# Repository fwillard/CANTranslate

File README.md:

# CANTranslate

## Overview

CANTranslate is a bridge solution that enables seamless communication ArduPilot devices using DroneCAN protocol and ODrive motor controllers using CANSimple protocol. It translates CAN bus messages between these two protocols in real-time, allowing for integration of these otherwise incompatible systems.

## Features

- Bidirectional translation between DroneCAN and CANSimple protocols
- Custom STM32F205 Based Hardware
- Support for critical message types from both protocols

## Hardware

CANTranslate runs on a custom PCB based on:

- STM32F205RGT6 microcontroller
- SN65HVD230 CAN Transciever

## Software

The project is written in C with the following components:

- Protocol parsers for both DroneCAN and CANSimple
- Message translation logic
- STM32 HAL CAN peripheral

## Protocol Support

### DroneCAN Messages

- [X] Node status messages
- [ ] Actuator commands 
- [ ] Sensor feedback

### CANSimple Messages

- [ ] Motor commands
- [ ] Encoder feedback
- [ ] Controller status
- [ ] Error codes

## License

This project uses dual licensing:

- **Software**: The software is licensed under the MIT License.
- **Hardware**: The hardware design files (schematics, PCB layouts, etc.) are licensed under the CERN Open Hardware License v2 - Permissive.

See the `LICENSE.md` file for the complete license text for both components.

## Contact

For questions and support, please open an issue on the GitHub repository.

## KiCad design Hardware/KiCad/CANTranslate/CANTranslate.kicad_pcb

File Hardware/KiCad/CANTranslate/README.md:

# CANTranslate – Hardware Design

## Overview

The hardware design for **CANTranslate** facilitates physical interfacing and electrical translation between multiple CAN bus systems. This includes power management, bus isolation, transceivers, and microcontroller integration for reliable embedded CAN communication.

## Features

* Dual SN65HVD230 CAN transceivers (CAN 2.0)&#x20;
* STM32F205RGT6 microcontroller
* Power input via USB or 5V pin on the CAN header
* Power source selection using TPS2116DRL (USB VBUS prioritized)
* Debug interface (SWD)

## Hardware Design Files

The following files are included in the `/Hardware/KiCad/CANTranslate` directory:

* `CANTranslate.kicad_pro`
* `CANTranslate.kicad_sch` – Schematic file
* `CANTranslate.kicad_pcb` – PCB layout
* `CustomParts.kicad_sym` – Custom symbol library
* `KMR223G LFG.STEP` – 3D model of tactile switch
* `fabrication-toolkit-options.json` – Fabrication preferences
* `fp-lib-table` – Footprint library table
* `sym-lib-table` – Symbol library table

## Power Requirements
* Power Inputs:
    * 5V from USB VBUS (primary source, with ESD protection)

    * 5V from the CAN header power pin (secondary source, no ESD protection)

* Power Selection:
    * The board uses a TPS2116DRL power multiplexer to automatically select the power source. When both USB and CAN header power are connected, the TPS2116DRL prioritizes USB VBUS, ensuring safe and seamless switching without back-feeding either source.

* Voltage Regulation:
    * The selected 5V supply is regulated down to 3.3V using an AMS1117-3.3 linear voltage regulator, providing stable power for the STM32F205RGT6 MCU and the SN65HVD230 CAN transceivers.

* Protection Features:
    * The USB power input includes ESD protection to safeguard against electrostatic discharge events.

## Toolchain

* **EDA Software**: KiCad 9.x

## Licensing

Hardware design files are released under the **CERN Open Hardware License v2** - Permissive

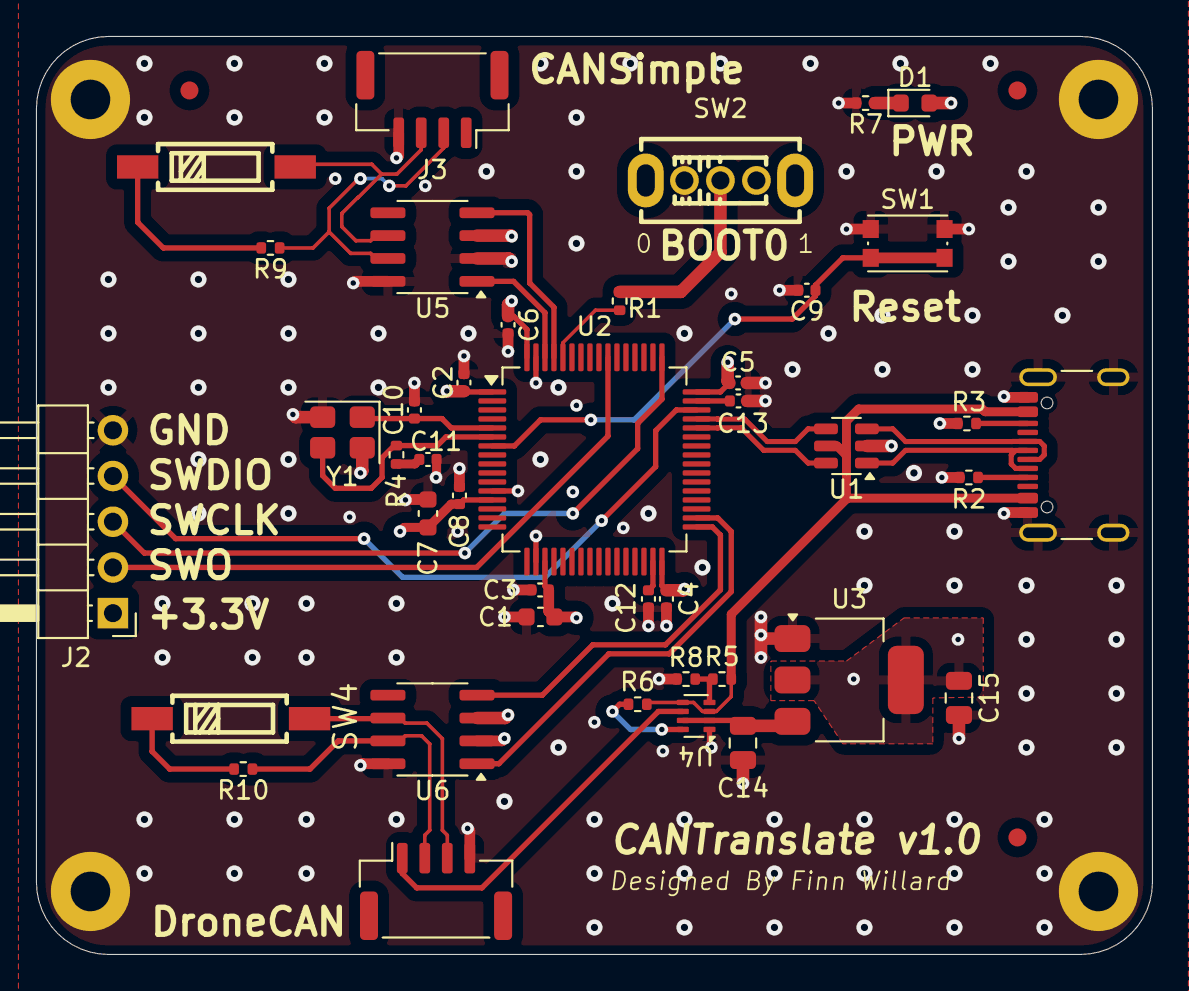
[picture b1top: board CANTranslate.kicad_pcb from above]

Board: 4 copper layers, 62.0 x 51.0 mm, 48 parts (0 on the bottom side), 35 nets.

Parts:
C1: 10u; C_0603_1608Metric
C2, C3, C4, C5, C6, C8, C9: 100n; C_0402_1005Metric
C7: 1u; C_0603_1608Metric
C10, C11: 10p; C_0402_1005Metric
C12, C13: 2u2; C_0402_1005Metric
C14, C15: 22u; C_0805_2012Metric
D1: RED; LED_0603_1608Metric
FID1, FID2, FID3: Fiducial; Fiducial_1mm_Mask2mm
H1, H2, H3, H4: MountingHole_Pad; MountingHole_2.2mm_M2_Pad
J1: USB_C_Receptacle_USB2.0_16P; USB_C_Receptacle_GCT_USB4105-xx-A_16P_TopMnt_Horizontal
J2: Conn_01x05_Pin; PinHeader_1x05_P2.54mm_Horizontal
J3, J4: SM04B-GHS-TB(LF)(SN); JST_GH_SM04B-GHS-TB_1x04-1MP_P1.25mm_Horizontal
R1, R6, R8: 10k; R_0402_1005Metric
R2, R3: 5k1; R_0402_1005Metric
R4: 470; R_0402_1005Metric
R5: 36k; R_0402_1005Metric
R7, R9, R10: 120; R_0402_1005Metric
SW1: SW_Push; SW_Push_1P1T_NO_CK_KMR2
SW2: SW_SPDT; SW-TH_SS12D07VG4
SW3, SW4: SW_SPST; SW-SMD_DSIC01LSGET
U1: USBLC6-2SC6; SOT-23-6
U2: STM32F205RGT6; LQFP-64_10x10mm_P0.5mm
U3: AMS1117-3.3; SOT-223-3_TabPin2
U4: TPS2116DRL; SOT-583-8
U5, U6: SN65HVD230; SOIC-8_3.9x4.9mm_P1.27mm
Y1: 16MHz; Crystal_SMD_3225-4Pin_3.2x2.5mm

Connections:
+3.3V: C1.1, C2.1, C3.1, C4.1, C5.1, C6.1, C7.1, C8.1, C15.1, D1.2 (A), J2.1, SW2.3 (C), U2.1 (VBAT), U2.13 (VDDA), U2.19 (VDD), U2.32 (VDD), U2.48 (VDD), U2.64 (VDD), U3.2 (VO), U5.3 (VCC), U6.3 (VCC)
+5V: J4.1, U4.6 (VIN2)
/BOOT0: R1.2, U2.60 (BOOT0)
/CAN1+: J3.2, R9.1, U5.7 (CANH)
/CAN1-: J3.3, SW3.1 (A), U5.6 (CANL)
/CAN1_RX: U2.61 (PB8), U5.4 (R)
/CAN1_TX: U2.62 (PB9), U5.1 (D)
/CAN2+: J4.2, R10.1, U6.7 (CANH)
/CAN2-: J4.3, SW4.1 (A), U6.6 (CANL)
/CAN2_RX: U2.33 (PB12), U6.4 (R)
/CAN2_TX: U2.34 (PB13), U6.1 (D)
/HSE_IN: C10.1, U2.5 (PH0), Y1.1
/HSE_OUT: R4.1, U2.6 (PH1), Y1.3
/NRST: C9.1, SW1.2, U2.7 (NRST)
/SWCLK: J2.3, U2.49 (PA14)
/SWDIO: J2.4, U2.46 (PA13)
/SWO: J2.2, U2.55 (PB3)
/S_BOOT0: R1.1, SW2.2 (B)
/USBCC1: J1.A5 (CC1), R2.1
/USBCC2: J1.B5 (CC2), R3.1
/USBC_D+: J1.A6 (D+), J1.B6 (D+), U1.3 (I/O2)
/USBC_D-: J1.A7 (D-), J1.B7 (D-), U1.1 (I/O1)
/USB_D+: U1.4 (I/O2), U2.45 (PA12)
/USB_D-: U1.6 (I/O1), U2.44 (PA11)
/VCAP_1: C12.1, U2.31 (VCAP_1)
/VCAP_2: C13.1, U2.47 (VCAP_2)
/V_OUT: C14.1, U3.3 (VI), U4.2 (VOUT), U4.7 (VOUT)
/V_PR1: R5.2, R8.1, U4.4 (PR1)
GND: C1.2, C2.2, C3.2, C4.2, C5.2, C6.2, C7.2, C8.2, C9.2, C10.2, C11.2, C12.2, C13.2, C14.2, C15.2, H1.1, H2.1, H3.1, H4.1, J1.A1 (GND), J1.A12 (GND), J1.B1 (GND), J1.B12 (GND), J1.S1 (SHIELD), J2.5, J3.4, J4.4, R2.2, R3.2, R7.2, R8.2, SW1.1, SW2.1 (A), U1.2 (GND), U2.12 (VSSA), U2.18 (VSS), U2.63 (VSS), U3.1 (GND), U4.1 (GND), U5.2 (GND), U5.8 (Rs), U6.2 (GND), U6.8 (Rs), Y1.2, Y1.4
unnamed: C11.1, R4.2
unnamed: D1.1 (K), R7.1
unnamed: R9.2, SW3.2 (B)
unnamed: R10.2, SW4.2 (B)
unnamed: R6.2, U4.8 (ST)
VBUS: J1.A4 (VBUS), J1.A9 (VBUS), J1.B4 (VBUS), J1.B9 (VBUS), R5.1, R6.1, U1.5 (VBUS), U4.3 (VIN1), U4.5 (MODE)

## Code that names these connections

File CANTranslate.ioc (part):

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Mcu.Name=STM32F205R(B-C-E-F-G)Tx
Mcu.Package=LQFP64
Mcu.UserName=STM32F205RGTx
PA11.Mode=Device_Only
PA11.Signal=USB_OTG_FS_DM
PA12.Mode=Device_Only
PA12.Signal=USB_OTG_FS_DP
PA13.Mode=Trace_Asynchronous_SW
PA13.Signal=SYS_JTMS-SWDIO
PA14.Mode=Trace_Asynchronous_SW
PA14.Signal=SYS_JTCK-SWCLK
PB12.Mode=CAN_Activate
PB12.Signal=CAN2_RX
PB13.Mode=CAN_Activate
PB13.Signal=CAN2_TX
PB3.Mode=Trace_Asynchronous_SW
PB3.Signal=SYS_JTDO-SWO
PB8.Mode=CAN_Activate
PB8.Signal=CAN1_RX
PB9.Mode=CAN_Activate
PB9.Signal=CAN1_TX
PH0-OSC_IN.Mode=HSE-External-Oscillator
PH0-OSC_IN.Signal=RCC_OSC_IN
PH1-OSC_OUT.Mode=HSE-External-Oscillator
PH1-OSC_OUT.Signal=RCC_OSC_OUT
RCC.HSE_VALUE=16000000
RCC.SYSCLKFreq_VALUE=120000000
RCC.SYSCLKSource=RCC_SYSCLKSOURCE_PLLCLK
board=custom

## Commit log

2025-04-27 Add libcanard to project
2025-05-04 Dronecan Simple Node setup
2025-05-04 add version info and unique hardware ids to node info
2025-05-04 remove git hash
2025-05-18 KiCad First Rev
2025-05-18 added readme and license
2025-05-18 added hardware readme
2025-05-18 fixed link issue
2025-05-25 initial RTOS setup
2025-05-25 restore cmake to build libcanard and dsdl
2025-05-25 building with DSDL
2025-05-25 restore additional files
2025-05-27 Switch project over from C6 to C8 MCU
2025-05-27 module changes
2025-05-27 clean up broken submodules
2025-05-27 Re-added DroneCAN submodules cleanly
2025-05-27 building for STMF103C8
2025-05-27 remove EWARM files
2025-05-30 Updated MCU from STM32F103C8T6 to STM32F303CCT6
2025-05-30 Update readmes to reflect new MCU type
2025-05-30 basic RTOS can loopback tx and rx for extended ids
2025-05-30 add micros64 function for timestamps
2025-05-31 basic heartbeat transmission
2025-05-31 make all tasks/queues/semaphores/mutexes static and reduce heap to 1kB
2025-05-31 logging statements and change defaultTask to statically allocated
2025-05-31 simple can rx isr
2025-05-31 get node info handling
2025-06-02 Fixed receive and put CAN in normal mode
2025-06-02 switch can transmit to single mailbox to ensure proper ordering of frames
2025-06-02 renamed time_utils to utils
2025-06-03 dynamic node id allocation
2025-06-03 change preffered node ic
2025-06-15 ESC testing
2025-06-18 initial odrive configs
2025-06-19 fix issue
2025-10-07 updated schematic to use two seprate CAN networks and different STM
2025-10-28 More Hardware Updates
2025-10-28 Can Simple troubleshooting
2025-10-28 Cube Changes
2025-10-28 git shenanigans
2025-10-29 Readme updates to reflect board changes
2025-10-29 basic build on STM32F205RG
2025-10-30 basic dronecan status working on F205 board
2025-10-30 Fixed unique id register and verified Dynamic node allocation working
2025-11-01 priority changes
2025-11-01 added logging over USB virtual com port
2025-11-01 Added ardupilot DSDL sources
2025-11-01 Added log level filtering
2025-11-01 added semaphore for tracking mailbox full
2025-11-01 Arm disarm odrive

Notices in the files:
README.md:
License: MIT & CERN-OHL-P-2.0
